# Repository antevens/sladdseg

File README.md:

# Sladdseg

Sladdseg is a wall plate that replaces a light switch on a circuit where every bulb is a smart bulb (here IKEA
Matter-over-Thread). The bulbs stay powered. An IKEA BILRESA scroll-wheel remote sits recessed in the plate and lifts
out; behind it a rocker switch cuts line and neutral to the circuit. The full edition adds mmWave presence,
temperature, humidity and push-to-talk voice at the switch location, powered from the box.

| North American single-gang (Decora) | European round flush box (DIN 49073) |
| --- | --- |
|  |  |

Two variants: **NA** for a 2 × 3 in single-gang box, **EU** for a Ø60 / 68 mm round flush box. Printed parts and
small PCBs, all generated from this repository.

## Design

- The remote is the control. The BILRESA sits in the plate, held by a magnet.
- The rocker is the fallback. Hidden behind the remote, it breaks line and neutral to the load and the plate's
  electronics; off and on brings the lights up without Home Assistant.
- Mains side: a certified rocker (Marquardt 1802.2504 or E-Switch RA412C1100), a certified 5 V supply and push-in
  terminal blocks, on a board designed to IEC 62368-1 spacing.

## Editions

| Edition | Remote | Mains board | Sensors | Face plate, NA | Face plate, EU |
| --- | --- | --- | --- | --- | --- |
| Switch | On its own cells | Rocker, terminal blocks | None | 69.85 × 114.3 mm (Decora) | 84.6 × 84.6 mm |
| Batt Free | Powered from the plate through spring pins, no cells | Rocker, terminal blocks, 5 V supply | None | 69.85 × 114.3 mm (Decora) | 84.6 × 84.6 mm |
| Full | Powered from the plate through spring pins, no cells | Rocker, terminal blocks, 5 V supply | Presence (mmWave, optional CO₂), temperature and humidity, push-to-talk microphone | 72.2 × 131.75 mm | 84.6 × 122.4 mm |

The barrier and the mains board are the same in every edition.

## What is on the plate

From the room inwards:

| Part | Material, place | Carries |
| --- | --- | --- |
| Face plate | PETG print, passive | Nothing: no electronics, no contacts, so it lifts off and goes back on blind. EU: snaps into a printed carrier that holds the sensor board |
| Sensor board | FR4, under the face plate, outside the box | The MSR-2 (ESP32-C3, LD2410B mmWave, optional CO₂) on its rear connector behind a thin radar skin; an SHT40 in a vented bay; a PDM microphone with its PDM-to-I²S converter. ESPHome over Wi-Fi; 5 V from the mains board |
| Barrier | PC-FR print, designed for a UL94 V-0 filament | The remote's pocket with the steel piece, the rocker's panel, and the wall between the mains volume and the low-voltage side |
| Pin board (Batt Free, Full) | FR4, in the box under the pocket floor | Two spring pins onto the back cover's pads |
| Mains board | FR4, in the box | The rocker, WAGO 2604 blocks for line, neutral and earth in and out, the 5 V supply on the switched side. The load runs in 0.5 mm copper bars on the front between the blocks and the rocker; every mains path sized for 15 A |

## Operation

Day to day the lights are controlled wirelessly: the remote, Home Assistant, the IKEA app or a voice assistant. The
rocker switch is for two cases:

- **Controller or network down:** turn the rocker switch off and on. The bulbs restart and come on at their power-on
  setting, which must be set to "On" in each bulb.
- **Safety:** off cuts line and neutral to the fixtures on this circuit and powers down the plate's electronics.

> **Warning: the rocker switch does not replace the breaker.** Turn the circuit's breaker off, and check with a
> tester that the wires are dead, before working on any wiring, the plate or the fixtures.

> **Warning: polarity matters.** Connect the supply's line to **L IN** and its neutral to **N IN**, as marked on the
> board, with the load wires on **L SW / N SW** (NA) or **L LOAD / N LOAD** (EU). Earth goes to **PE** on the NA board;
> on the EU plate it is joined in the box with a WAGO 221-412 lever connector. The PSU's fuse is
> in the line; with line and neutral swapped, the fuse sits in the neutral and line stays on the PSU when it blows.
> Confirm which supply wire is line with a tester before connecting.

The microphone (full edition) streams to Home Assistant's Assist pipeline only when listening is started from Home
Assistant. There is no wake word and no speaker.

## North American single-gang / Decora

Full edition:

| Remote in place | Remote out, rocker switch exposed |
| --- | --- |
|  |  |

| Half-section | Back, box side |
| --- | --- |
|  |  |

Exploded, front to back: remote, face plate, barrier, sensor board with the MSR-2, pin board with the spring pins on
two spacer posts, four nylon standoffs, mains board.

Switch edition:

| Remote in place | Remote out, rocker switch exposed |
| --- | --- |
|  |  |

Batt Free edition:

| Remote in place | Remote out, rocker switch exposed |
| --- | --- |
|  |  |

## European round flush box (DIN 49073)

The barrier closes the box and carries the remote; under it the mains board at the rocker's seat and the pin board;
on the wall the sensor board in a printed carrier, and the face plate snapped into the carrier.

Full edition:

| Remote in place | Remote out, rocker switch exposed |
| --- | --- |
|  |  |

| Half-section | Back, box side |
| --- | --- |
|  |  |

On the back: the mains board with its two WAGO push-in blocks (grey) and the PSU (black); the pin board sits between
it and the barrier.

Switch edition:

| Remote in place | Remote out, rocker switch exposed |
| --- | --- |
|  |  |

Batt Free edition:

| Remote in place | Remote out, rocker switch exposed |
| --- | --- |
|  |  |

## Battery-free back cover

For fixed installs: the printed cover replaces the remote's own and runs it from the plate with no cells; lifted
out, the remote is off. Two pads behind windows in the cover's back take 5 V from the spring pins, and a 3.3 V
regulator on the cover's flex feeds two spring fingers on the remote's battery contacts. Not a charging circuit; it
holds no energy.

| Cover with its flex | Exploded in the EU plate |
| --- | --- |
|  |  |

## Building from source

CAD in Python (build123d); boards in Python to KiCad 9 projects (ERC and DRC clean, schematic parity); slicer
projects; PCBWay packs; order lists with live DigiKey and Mouser stock. `make check`
includes a test that no air path leads from the mains volume through the printed barrier to the room.

```bash
make system-deps     # once, Ubuntu 24.04 (KiCad 9, headless slicer libs)
make setup           # once (venv + pinned ElegooSlicer)
make pcb             # boards: ERC / DRC, STEP, fab packs
make cad check       # CAD to build/, all checks (shared parts, NA, EU)
make na              # NA variant: CAD, checks, renders
make eu              # EU variant: CAD, checks, renders
make print           # ElegooSlicer projects in print/
make renders         # docs/renders/*.png
make order           # DigiKey / Mouser lists, PCBWay packs
```

| Document | Contents |
| --- | --- |
| [`AGENTS.md`](AGENTS.md) | Project overview, rules, status, backlog |
| [`docs/SAFETY.md`](docs/SAFETY.md) | Safety notes and limits |
| [`docs/DESIGN.md`](docs/DESIGN.md) | Requirements and decision log |
| [`docs/BOM.md`](docs/BOM.md) | Parts per plate |
| [`docs/ASSEMBLY.md`](docs/ASSEMBLY.md) | What holds each part, assembly order, detail views |
| [`docs/PRINTING.md`](docs/PRINTING.md) | Print jobs, settings, order of work |
| [`docs/MEASUREMENTS.md`](docs/MEASUREMENTS.md) | Measured values and the ones still estimated |
| [`pcb/README.md`](pcb/README.md) | All seven boards: what each carries, editions, status |
| [`pcb/na/README.md`](pcb/na/README.md), [`pcb/eu/README.md`](pcb/eu/README.md), [`pcb/shared/README.md`](pcb/shared/README.md) | Each variant's boards and the shared cover flex in detail: parts, nets, rules, board renders |
| [`pcb/order/README.md`](pcb/order/README.md) | DigiKey / Mouser order lists and PCBWay packs |

## Status

- **Ready to order:** the NA and EU mains boards and both pin boards have PCBWay packs, after
  the human review in [`pcb/na/fab/README.md`](pcb/na/fab/README.md) and [`pcb/eu/fab/README.md`](pcb/eu/fab/README.md).
- **Not ready to order:** the NA and EU sensor boards (CN2's position on the MSR-2 is a photo estimate) and the back cover
  flex (contact positions not yet measured on a remote).
- **To measure:** the `MEASURE` and `ESTIMATE` values in [`docs/MEASUREMENTS.md`](docs/MEASUREMENTS.md).
- **Not started:** the ESPHome configuration for the MSR-2 with the SHT40 and the microphone.

## Open items

Suitable for a contribution:

- a back cover with a battery and a charger;
- a UK variant (86 mm plate, shallow back box);
- a version for the BILRESA dual-button remote (IKEA E2489);
- a jumbo-plate option.

[`AGENTS.md`](AGENTS.md) has the conventions, the hard constraints and the checks that must stay green.

## Cost (2026-10-12)

Parts and PCBs per plate, USD.

| Package | 1 plate | 5 plates | 100 plates | 1,000 plates | 10,000 plates |
| --- | --- | --- | --- | --- | --- |
| NA full | 110.90 | 59.68 | 37.61 | 34.19 | 32.48 |
| NA full + MSR-2 | 148.89 | 97.67 | 75.60 | 72.18 | 70.47 |
| NA full + MSR-2 with CO2 | 168.89 | 117.67 | 95.60 | 92.18 | 90.47 |
| NA switch only | 20.68 | 15.96 | 10.00 | 9.06 | 8.60 |
| NA battery-free | 68.71 | 38.63 | 24.87 | 22.61 | 21.47 |
| EU full | 102.61 | 48.95 | 31.13 | 28.37 | 26.99 |
| EU full + MSR-2 | 140.60 | 86.94 | 69.12 | 66.36 | 64.98 |
| EU full + MSR-2 with CO2 | 160.60 | 106.94 | 89.12 | 86.36 | 84.98 |
| EU switch only | 15.59 | 9.18 | 6.64 | 6.04 | 5.74 |
| EU battery-free | 60.83 | 29.26 | 19.24 | 17.55 | 16.70 |

Sources and assumptions:

- **Parts at 1, 5 and 100 (sourced):** DigiKey US list prices for the order lists' parts (`pcb/order/`), cheapest
  packaging and price break for the total need, read 2026-10-12. Per plate:
  - 1 plate: NA full 50.97, NA battery-free 33.71, NA switch only 15.68; EU full 42.17, EU battery-free 25.83,
    EU switch only 10.59.
  - 5 plates: NA full 47.70, NA battery-free 31.63, NA switch only 14.96; EU full 36.86, EU battery-free 22.26,
    EU switch only 8.18.
  - 100 plates: NA full 34.20, NA battery-free 22.64, NA switch only 9.36; EU full 27.60, EU battery-free 16.92,
    EU switch only 6.00.
- **Parts at 1,000 and 10,000 (assumption):** 10 % and 15 % below the 100-plate price. DigiKey shows no prices
  above about 100 without a quote.
- **PCBs at 1 and 5 (sourced):** PCBWay's 5-piece minimum order, 2026-10-12; one plate pays for the whole order.
  - Mains board, pin board, EU mains board, EU pin board: 5.00 each order.
  - Sensor board 24.93, EU sensor board 25.44.
  - Cover flex: about 25 (estimate).
  - Per plate: 1 plate NA full 59.93, NA battery-free 35.00, EU full 60.44, EU battery-free 35.00, switch only
    5.00 (the mains board alone); 5 plates one fifth of that.
- **PCBs at 100 (sourced):** PCBWay quotes for 100 pieces, 2026-10-12.
  - Mains board 0.64, sensor board 1.17, pin board 0.36.
  - EU mains board 0.64, EU pin board 0.45, EU sensor board 1.21.
  - Cover flex 1.24.
  - Per plate: NA full 3.41, NA battery-free 2.23, EU full 3.53, EU battery-free 2.32, switch only 0.64.
- **PCBs at 1,000 and 10,000 (assumption):** the 100-piece price (no quote). This is cautious: board prices
  usually fall at volume.
- **MSR-2 (assumption):** Apollo's retail price at every quantity, 37.99 base and 57.99 with CO2. No volume price
  is published.

Known gaps:

- **Quote specs differ from the design:**
  - The mains boards were quoted with 1 oz copper; the NA board is 2 oz. The copper bars are not quoted.
  - The pin board was quoted at 1.6 mm, not 0.8.
- **Not included:**
  - PCB assembly (the sensor board, the EU sensor board and the cover flex need it);
  - the IKEA remote;
  - printed parts, screws and heatshrink;
  - shipping and duties.
- **Cheaper terminal blocks:** Same Sky TBL-0021-500-06GR (NA) and TBL-0020-500-02GR (EU), push-in without a lever,
  fit the WAGO 2604 footprint and cost about 5–6 (NA) and 3 (EU) less per plate at 100. Not in the design.

### Printed parts (own printer, 2026-10-13)

The barrier (one per variant, printed with the blank board for switch only, D-127) is printed in Elegoo PC-FR; the
face plate, the EU carrier and the back cover in Elegoo PETG. Grams and times come from the slicer projects
(`make print`). USD per plate.

| Package | Printed parts | Filament | Print time | Filament cost | Electricity | Printer wear | **Total** |
| --- | --- | --- | --- | --- | --- | --- | --- |
| NA full | Barrier and blank board 52.5 g PC-FR; face plate 23.8 g, back cover 8.1 g PETG | 84.4 g | 3.5 h | 1.56 | 0.08 | 0.31 | **1.94** |
| NA switch only | Barrier and blank board 52.5 g PC-FR; face plate 16.7 g PETG | 69.2 g | 2.8 h | 1.39 | 0.06 | 0.25 | **1.70** |
| NA battery-free | Barrier and blank board 52.5 g PC-FR; face plate 16.7 g, back cover 8.1 g PETG | 77.3 g | 3.2 h | 1.48 | 0.07 | 0.28 | **1.84** |
| EU full | Barrier and blank board 13.3 g PC-FR; face plate 43.3 g, carrier 18.5 g, back cover 8.1 g PETG | 83.3 g | 3.0 h | 1.08 | 0.07 | 0.27 | **1.41** |
| EU switch only | Barrier and blank board 13.3 g PC-FR; face plate 30.2 g, carrier 8.6 g PETG | 52.1 g | 1.9 h | 0.73 | 0.04 | 0.17 | **0.94** |
| EU battery-free | Barrier and blank board 13.3 g PC-FR; face plate 30.2 g, carrier 8.6 g, back cover 8.1 g PETG | 60.2 g | 2.3 h | 0.82 | 0.05 | 0.20 | **1.08** |

Sources and assumptions:

- **Filament (sourced):** Elegoo US store, 10 kg packs, read 2026-10-12.
  - PC-FR: 229.99, 23.00 / kg (1 kg spool 34.99).
  - PETG Pro: 109.99, 11.00 / kg (1 kg spool 13.99).
- **PETG weights (assumption):** the face plates and carriers are sliced in PLA only. Their weight is scaled by
  the density ratio (PETG 1.27 / PLA 1.24) at the same print time.
- **Electricity (assumption):** 150 W average at 0.15 / kWh.
- **Printer wear (assumption):** about 440 for the CC2 Combo (Elegoo's bundles list at 435–499) over 5,000 print
  hours.
- **Not included:** labour, failed prints, bed adhesive.
- **Print services:** not quoted.

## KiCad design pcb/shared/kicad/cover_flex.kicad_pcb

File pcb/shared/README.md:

# Shared board (v0.7)

The replacement back cover's flex (D-35, D-50), the same board in both variants, and the generator for every
low-voltage board: `tools/gen_lv.py na|eu|shared` writes the NA sensor and pin boards into `../na/kicad/`, the EU
sensor board into `../eu/kicad/` and the cover flex into `kicad/`, each folder with the low-voltage library (`lv.pretty`,
`lv.kicad_sym`). Parts both variants share (the CN2 mate, the microphone and its parts, footprints, the flex) are in
`tools/lv_parts.py`; each variant's boards in `../na/tools/lv_parts_na.py` and `../eu/tools/lv_parts_eu.py`. Geometry
comes from `cad/build123d/params.py` (the CAD model is in `cad/build123d/backcover.py`).

Nothing here touches mains.

## Back cover flex (`kicad/cover_flex.*`)

Single copper layer, polyimide, for the replacement back cover that powers a BILRESA E2490
without cells (`cad/build123d/backcover.py`, DESIGN D-35). Drawn flat, seen from the copper side.

- J1, J2: gold pads (+5V, GND) on the pad section, which lies copper down on a ledge in the
  cover, behind Ø2.1 windows in its back: the plate's spring pins press on them (NA, D-50). Ø3.0 copper
  under a Ø2.6 coverlay opening: the coverlay holds the pad's edge (D-116).
- A 2.6 mm run (in a notch along the GND contact post's inner face, D-79) to the terminal end; one 90°
  bend, inside r 0.6 mm (6 × the 0.10 mm flex), copper outside, with a relief slit either side of the
  run so the rest of the end section reaches down to the ledge (D-116). The tracks cross the bend zone
  straight; the +3V3 lane turns 0.85 mm past it.
- J1 takes +5 V from the plate (D-41, D-50); D1 TI TPD1E10B06DYAR (ESD) on +5V; U1 TI TLV75533PDBVR (3.3 V,
  SOT-23-5) with C3 / C4 1 µF 0603 X5R (0.85 µF or more at their working voltages) on the regulator section,
  copper down in a recess in the cover (0.4 mm wall left), feeds VBAT (D-116).
- A 0.8 mm FR4 stiffener (back side) on the pad and regulator sections, flush with their long
  edges: five snap hooks in the cover hold it down against the pins' push (D-45, D-79); 0.15 mm under
  the hooks for the stiffener's tolerance and adhesive (D-116). No holes.
- Coverlay openings 0.1 mm beyond the pads, one opening over each pin row of U1 / D1; teardrops where the
  tracks leave the pads (D-116).
- J3, J4: Harwin S7081-42R spring fingers (VBAT, GND) on the end section, on the cell axes, long
  axis vertical with the bend end up (the battery contacts ride down the arm's ramp as the cover
  goes on), on a 0.4 mm FR4 stiffener (back side), notched round the run 0.76 mm past the bend zone; it slides
  down slots along the contact blocks (D-55). The end section stands 2.0 mm (the fingers'
  working height) in from the cell end plane: J3 presses the remote's fixed VBAT plate, J4 its GND
  leaf spring (finger and leaf share the travel). Between them only a band passes under the
  remote's PCB strip.

Not ready to fabricate: the positions come from the FCC internal photos (REF) or are MEASURE;
`tools/build.sh` writes no `fab/cover_flex/` while `COVER_CONFIRMED` is false.

## Microphone firmware (D-29, D-83)

ESPHome on the MSR-2, push-to-talk: Home Assistant starts listening (for example from a BILRESA
button automation calling the action) and the voice pipeline ends it on silence. Untested
starting point:

```yaml
i2s_audio:
  - id: i2s_mic_bus
    i2s_lrclk_pin: GPIO6
    i2s_bclk_pin: GPIO4

microphone:
  - platform: i2s_audio
    id: plate_mic
    i2s_audio_id: i2s_mic_bus
    adc_type: external
    i2s_din_pin: GPIO7
    channel: left              # SELECT low: check which slot carries the mic on an MSR-2
    bits_per_sample: 32bit     # ADAU7002: 20-bit data in 32-bit slots, BCLK = 64 x fs
    sample_rate: 16000         # PDM clock 64 x fs = 1.024 MHz: the mic's performance mode starts at 1.0 MHz

voice_assistant:
  microphone: plate_mic

api:
  actions:
    - action: start_listening
      then:
        - voice_assistant.start:
    - action: stop_listening
      then:
        - voice_assistant.stop:
```

Open: whether the pipeline accepts 48 kHz from this microphone on the C3 or needs 32 kHz, and
the C3's RAM / CPU headroom next to the radar, Wi-Fi and BLE.

## Regenerate

```bash
make pcb        # every board; or pcb/shared/tools/build.sh for the cover flex alone
```

`tools/build.sh` writes the 3D models and the cover flex (`tools/gen_lv.py shared`), runs ERC and DRC (all severities,
schematic parity; reports in `build/`) and writes `fab/cover_flex/` once its positions are measured
(`COVER_CONFIRMED`).

## Open

- CN2 mate (Molex 55909-2474, D-82, D-89): contact map and pin 1 (from the GPIO add-on's plug or Apollo). Then set
  `CN2_CONFIRMED`, regenerate, check the fan-out. The pads' mask webs are 0.18 mm (PCBWay: 0.19 green): one opening
  per row.
- The FFC passes through the mains volume to the barrier's slit (SAFETY item 4).
- MK1 and U2 pin 1 against parts (footprints from the datasheets' top views).
- Microphone firmware test on an MSR-2 (sample rate, I²S slot, load).

## Renders

The cover flex with components, without them, and its copper layer.

| Back cover flex, copper side | Back cover flex, stiffener side |
| --- | --- |
|  |  |
|  |  |

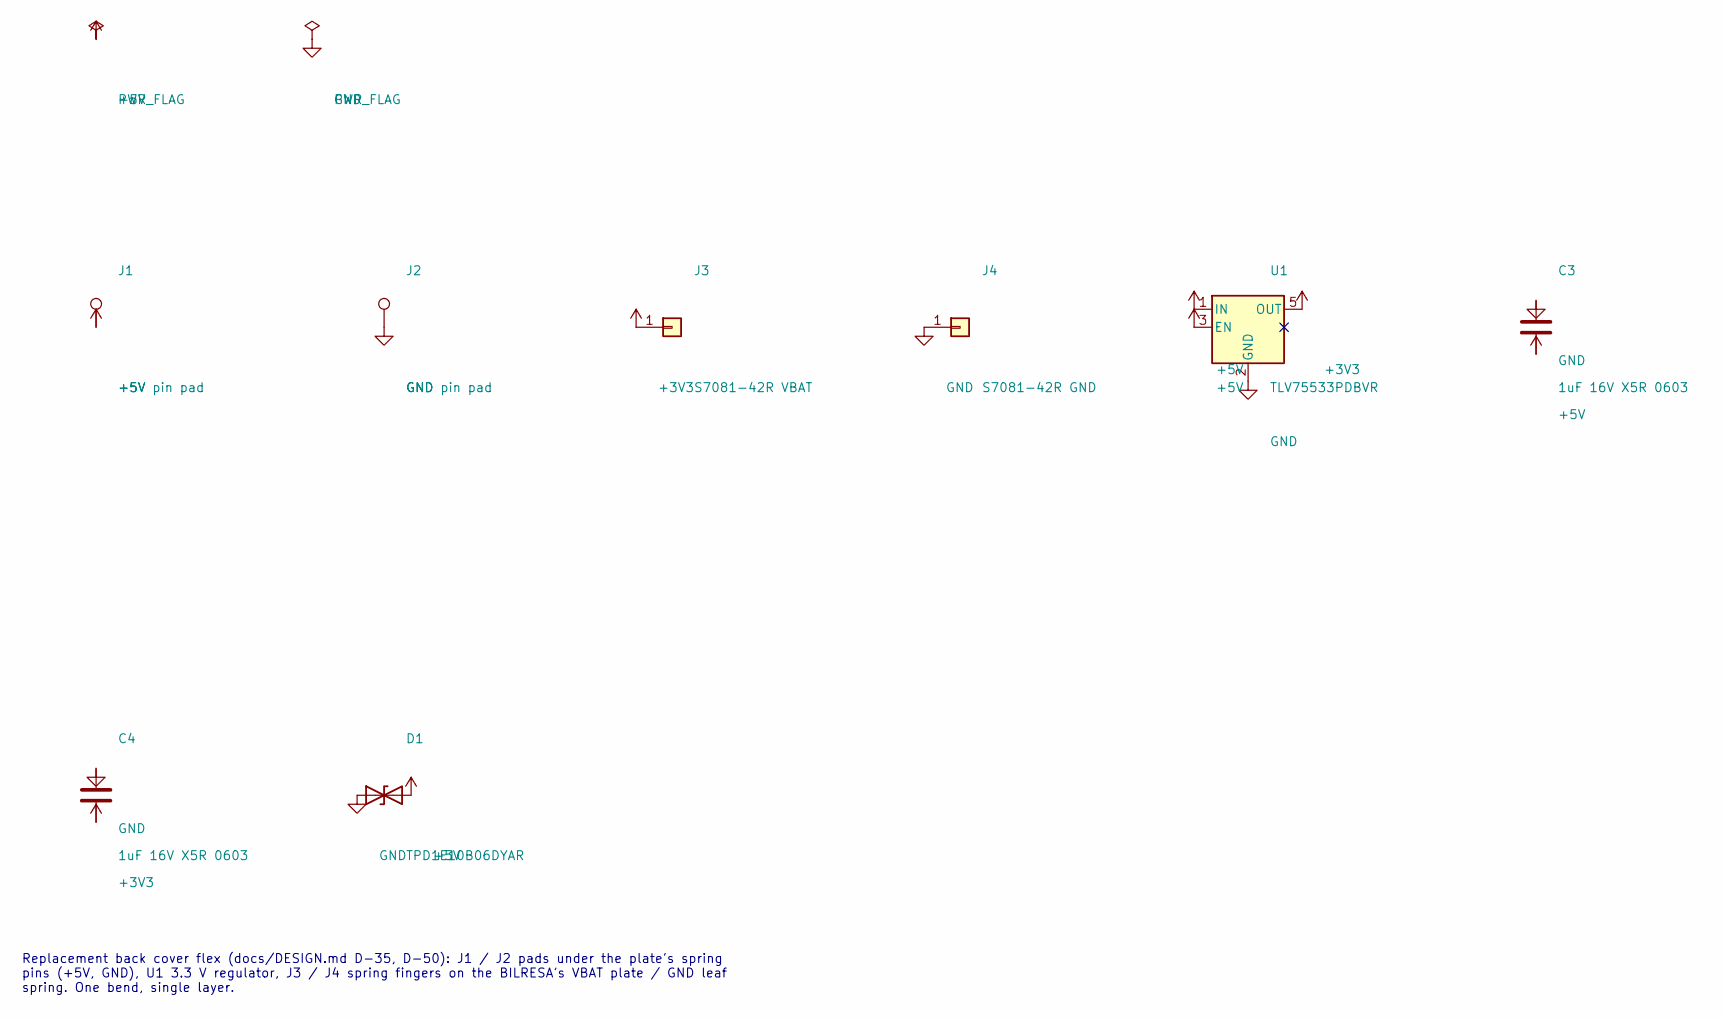
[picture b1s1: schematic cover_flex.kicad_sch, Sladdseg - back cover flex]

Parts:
C3, C4: 1uF 16V X5R 0603; C_0603_1608Metric; MPN CL10A105KO8NNNC
D1: TPD1E10B06DYAR; D_SOD-523_TI_DYA0002A; MPN TPD1E10B06DYAR
J1: +5V pin pad; Contact_Pad_D2.6mm
J2: GND pin pad; Contact_Pad_D2.6mm
J3: S7081-42R VBAT; Harwin_S7081-42R; MPN S7081-42R
J4: S7081-42R GND; Harwin_S7081-42R; MPN S7081-42R
U1: TLV75533PDBVR; SOT-23-5; MPN TLV75533PDBVR

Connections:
+3V3: C4.2, J3.1, U1.5 (OUT)
+5V: C3.2, D1.2 (A2), J1.1, U1.1 (IN), U1.3 (EN)
GND: C3.1, C4.1, D1.1 (A1), J2.1, J4.1, U1.2 (GND)

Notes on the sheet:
Replacement back cover flex (docs/DESIGN.md D-35, D-50): J1 / J2 pads under the plate's spring pins (+5V, GND), U1 3.3 V regulator, J3 / J4 spring fingers on the BILRESA's VBAT plate / GND leaf spring. One bend, single layer.

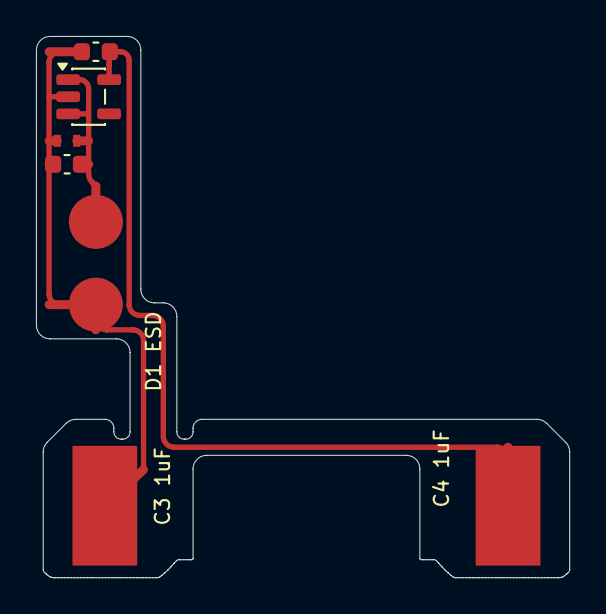
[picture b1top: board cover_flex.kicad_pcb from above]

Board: 2 copper layers, 29.6 x 30.1 mm, 8 parts (0 on the bottom side), 3 nets.

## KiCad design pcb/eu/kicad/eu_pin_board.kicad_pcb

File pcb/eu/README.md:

# EU boards (v0.7)

The European plate's boards (round flush box, DIN 49073, Ø60 inside): the mains board and the pin board, both
hanging from bosses under the barrier, from `tools/gen_eu.py` with their parts in `tools/parts_eu.py` (D-30, D-36); the
sensor board in the carrier from `../shared/tools/gen_lv.py eu`, its parts in `tools/lv_parts_eu.py` (D-56, D-70).
Geometry from `cad/build123d/params.py` and `cad/build123d/eu/params_eu.py`. The back cover's flex, the same for both
variants, is in `../shared/README.md`.

Spacing values are design targets for human review. Nothing here is a compliance claim.

## Mains board (`kicad/eu_mains_board_busbar.*`, fab pack in `fab/eu_mains_board_busbar/`)

Round, at the rocker's PCB seat (16.2 mm below its panel face). The rocker breaks line and neutral
of the lights; the PSU is fed from the switched side, so the rocker also turns the sensor off. The lights' current
runs in four copper bars on the front (D-153); the earlier board with the load in pours on high-CTI FR4 is dropped
(D-155).

| Ref | Part | Side | Nets |
| --- | --- | --- | --- |
| S1 | Marquardt 1802.2504 rocker, DPST, PCB pins, ENEC 12(4) A 250 V~, UL/CSA 15 A; second source E-Switch RA412C1100 (4.8 mm tabs, ENEC 10(4) A, D-88): plated slots 5.2 × 1.2 on 10.2 × 7.05, their pads up to the WAGO bodies (0.05 mm), 3.85 mm from the WAGO pins (D-153) | front (through the barrier's panel) | 1 L_IN, 1a L_SW, 2 N_IN, 2a N_SW |
| J1 | WAGO 2604-3102, push-in, 2-pole, 4 mm², entry 90° to the board, 400 V III/2; turned 180° from J2 | back | L_SW (pole 1), L_IN (pole 2, upper) |
| J2 | WAGO 2604-3102 (as J1) | back | N_IN (house neutral), N_SW (to the lights) |
| F1 | Schurter UMT 250, T1A 250 VAC | front | L_SW to L_F |
| RV1 | TDK CU4032K275G2, 275 VAC | front | L_F to N_SW |
| PS1 | Zettler ZPI03S0500WC, 5 V 600 mA (UL/EN 62368-1, EN 61558-2-16; I/P-O/P 3600 VAC; reinforced / OVC not stated: review, D-100) | back | inputs L_F / N_SW above the slot, outputs +5V / GND below it |
| J3 | Samtec TSM-102-02-L-SV, SMT pin header 1x2, 2.54 mm, 8.13 mm post (no pin tails under the PSU) | front, 5 V island | +5V, GND |
| MH1-MH3 | M2 holes on the barrier's long bosses | - | - |

- The lights' current runs in four straight 0.5 mm copper bars soldered on the front, one along each WAGO pole's pin
  row to the rocker (`BB_BARS`: in bars above their row, switched below it, round ends past the outer pin, clear of
  the 6 mm barrier bosses); no load pours. Built by `gen_eu.py busbar`; `tools/bars_eu.py` (CAD Python) draws the
  bars round the pads (`build/eu_mains_board_pads.json`), checks them and writes `kicad/eu_mains_board_busbar_bars.json`
  (their lands: copper with no solder mask) and the DXF for the laser cutter. WAGO pin rows and body from WAGO's 3D
  model (8.2 mm apart, levers towards the board centre, where the blocks' pins stay 1.0 mm clear of the rocker body
  on the front); blocks at x ±16.6, y 7.5. Short links from the bars to F1 and to the RV1 / PSU feed (1.0 mm track).
  Standard FR4, 1 oz (no PE on the board), HASL lead-free.
- A routed relief slot under the PSU, between its input and output rows, cuts off the 5 V island
  (PSU outputs, J3). Mains copper keeps ≥ 8 mm (clearance and creepage) from it.
- Keep-out areas round the mounting holes: mains copper ≥ 1.0 mm from them.
- No PE on the board: the lights' protective earth is joined in the box in a WAGO 221-412 lever connector, in the
  order lists (D-94; a third PE conductor takes a 221-413).
- Installer labels on the back: L IN / L LOAD, N IN / N LOAD at the WAGO blocks, MAINS 230 VAC.

## Pin board (`kicad/eu_pin_board.*`, fab pack in `fab/eu_pin_board/`)

D-shaped, just under the barrier, cut below the switch cup; a hole lets the mains board's lower long
boss through. No mains on it.

| Ref | Part | Side | Nets |
| --- | --- | --- | --- |
| J1 | Samtec SSW-102-01-G-S pin socket 1x2, 2.54 mm (8.5 mm), on the mains board's J3 | back | +5V, GND |
| C1 | 22 µF 10 V X5R 1206 | front | +5V to GND |
| P1, P2 | Harwin P70-2200045 SMT spring pins with pegs, 2 A | front | GND (P1, upper), +5V (P2): through the barrier onto the sensor board's pads (D-56, D-59, D-70) |
| P3, P4 | Harwin P70-2200045 SMT spring pins with pegs, 2 A | front | +5V (P3, upper), GND (P4): through the barrier onto the battery-free back cover's pads (D-54, D-79) |
| MH1, MH2 | M2 holes on the barrier's bosses | - | - |

The header posts reach 3.07 mm into the socket (boards 16.1 mm apart, D-59; check with the parts).
Nothing is soldered or wired between the boards or across the barrier (DESIGN R9, R10).

## Sensor board (`kicad/eu_sensor_board.*`)

FR4 1.6 mm, two layers, round the remote pocket in the barrier's printed carrier (its rim round the board). TP1 / TP2:
Ø2.4 gold pads on the underside under the pin board's sensor spring pins (GND, +5V). As on the sensor board: J2 mates
the MSR-2's CN2 (Hirose DF40C-24DP-0.4V(51), Apollo's contact map, D-154) and H5–H7 (Würth WA-SMSI 9774015243R, 1.5 mm) carry its board under the face plate's
posts; MK1 and U2 with C3, C4 and R1 as on the sensor board (`route_mic`, D-83), the mic at x 32.0 so its parts and
lanes sit between it and the MSR-2's bay frame. I²S from CN2's signal row (the lower one) down, right, down and into U2,
+3V3 down to a via and on the back to the parts' +3V3; SDA and SCL out past the header's ends to vias; SDA, SCL and
+3V3 (from the parts' +3V3) on the back
down the outer left edge (outside the snap windows and the screws) to U1 (SHT40) and C2 at the bottom; +5V from the
pin pad on the back up the outer right edge and across to a via above CN2's +5V contact; GND pours on both layers; 0.45 / 0.2 mm vias round CN2. Windows at
the four corners pass the face plate's snap fingers; notches in the top edge clear the MSR-2's back switches. H1–H4:
holes for the M2 screws into the carrier. Fit-test prototype: CN2's position on the MSR-2 is a photo estimate.

## Rules

`kicad/eu_mains_board_busbar.kicad_dru`: L–N ≥ 3.2 mm, any two different mains nets ≥ 3.2 mm (line / switched
line / fused line, neutral / switched neutral; `BB_GAP`: IEC 60664-1 creepage at the 320 V row, pollution degree 2,
material group III, standard FR4, D-153), mains to the 5 V side ≥ 8.0 mm (clearance and creepage), mains copper
≥ 1.0 mm from the board edge and the holes; pins of one rated part keep the part's own spacing. Design targets for
human review, not a compliance claim.

The net classes come from the project file; `tools/gen_eu.py` rewrites it after every save
(pcbnew's SaveBoard resets it). The single EU PSU board before D-36 was checked without them, so
its isolation was never verified by DRC.

## Regenerate

```bash
make pcb        # every board; or pcb/eu/tools/build.sh for the EU boards alone
```

`tools/build.sh` writes the 3D models, the mains board and the pin board (`gen_eu.py`) and the sensor board
(`../shared/tools/gen_lv.py eu`), runs ERC and DRC on all three, and writes the PCBWay packs for the mains board and
the pin board in `fab/` (`fab/README.md`: order settings and the review checklist). Order only after the review and a
dry fit of the stack in a real box. The sensor board's PCBWay files are a fit-test prototype (D-154).

## Renders

Each board with components, without them, and its copper layers (back seen from behind).

| Mains board, front | Mains board, back |
| --- | --- |
|  |  |
|  |  |
|  |  |

Dropped board (D-155), its files still in the tree until backlog item 4 removes them: `kicad/eu_mains_board.*`,
`fab/eu_mains_board/`, `build/eu_mains_board.step` and the renders `docs/renders/eu_mains_board_front.png`,
`docs/renders/eu_mains_board_back.png`, `docs/renders/eu_mains_board_bare_front.png`,
`docs/renders/eu_mains_board_bare_back.png`, `docs/renders/eu_mains_board_copper_front.png`,
`docs/renders/eu_mains_board_copper_back.png`, `docs/renders/eu_mains_board_bare_iso.png`.

| pin board, front | pin board, back |
| --- | --- |
|  |  |
|  |  |
|  |  |

| Sensor board, front | Sensor board, back |
| --- | --- |
|  |  |
|  |  |
|  |  |

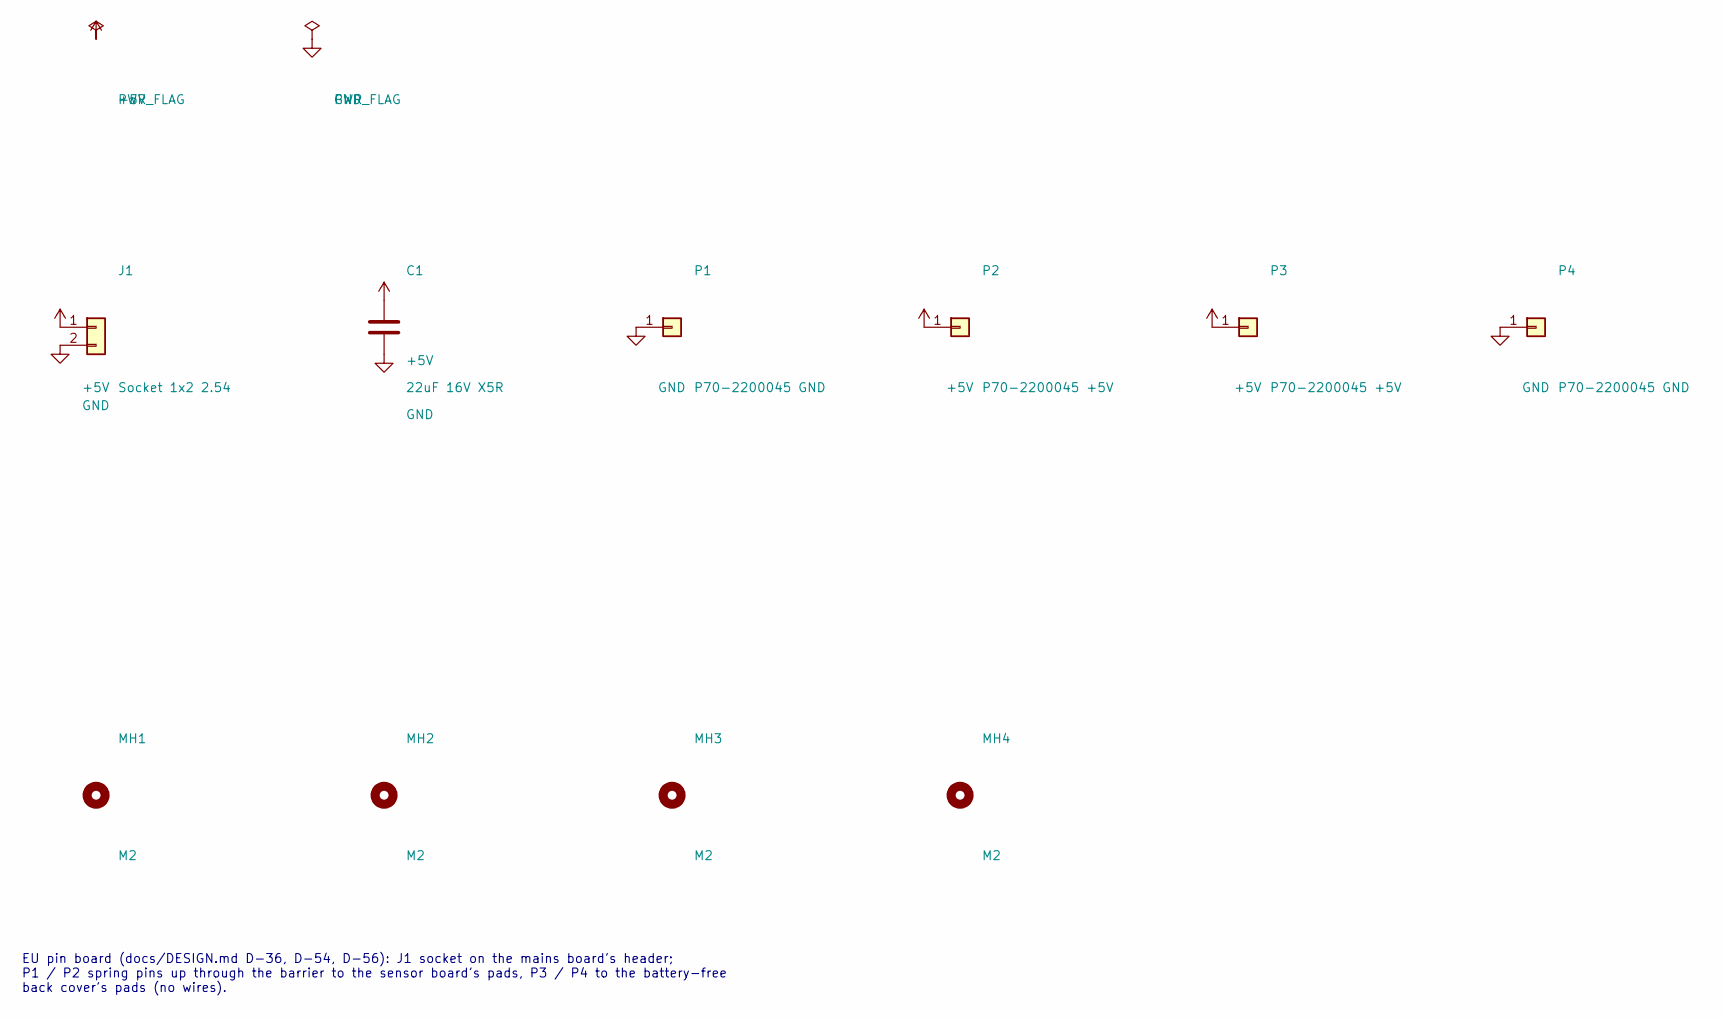
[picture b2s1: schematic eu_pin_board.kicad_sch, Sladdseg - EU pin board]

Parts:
C1: 22uF 16V X5R; C_1206_3216Metric; MPN C1206C226M4PACTU
J1: Socket 1x2 2.54; PinSocket_1x02_P2.54mm_Vertical; MPN SSW-102-01-G-S
MH1, MH2, MH3, MH4: M2; MountingHole_2.2mm_M2
P1, P4: P70-2200045 GND; Harwin_P70-2200045; MPN P70-2200045
P2, P3: P70-2200045 +5V; Harwin_P70-2200045; MPN P70-2200045

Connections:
+5V: C1.1, J1.1, P2.1, P3.1
GND: C1.2, J1.2, P1.1, P4.1

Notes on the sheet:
EU pin board (docs/DESIGN.md D-36, D-54, D-56): J1 socket on the mains board's header; P1 / P2 spring pins up through the barrier to the sensor board's pads, P3 / P4 to the battery-free back cover's pads (no wires).

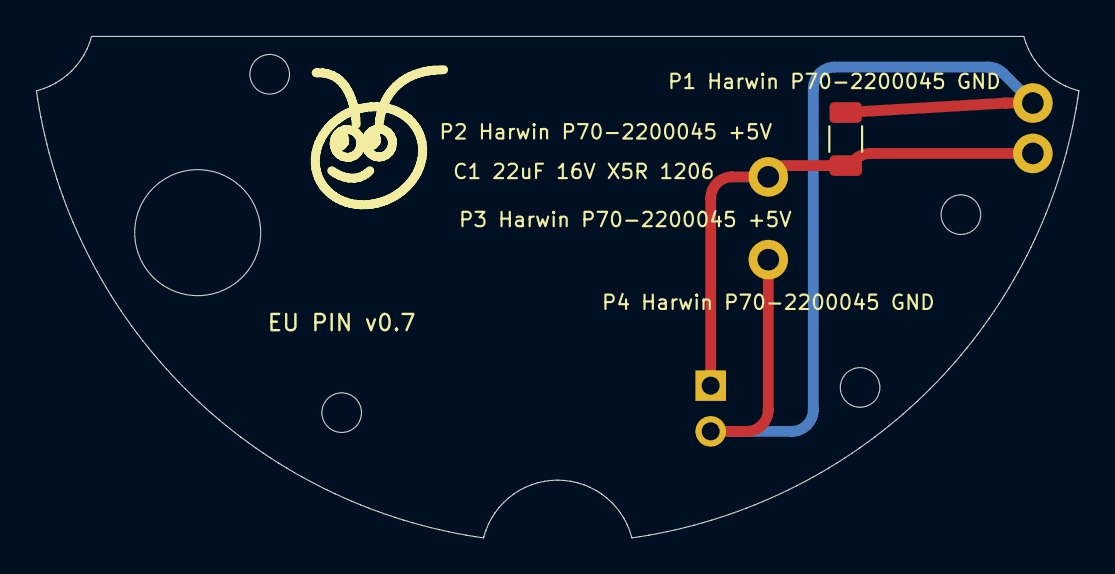
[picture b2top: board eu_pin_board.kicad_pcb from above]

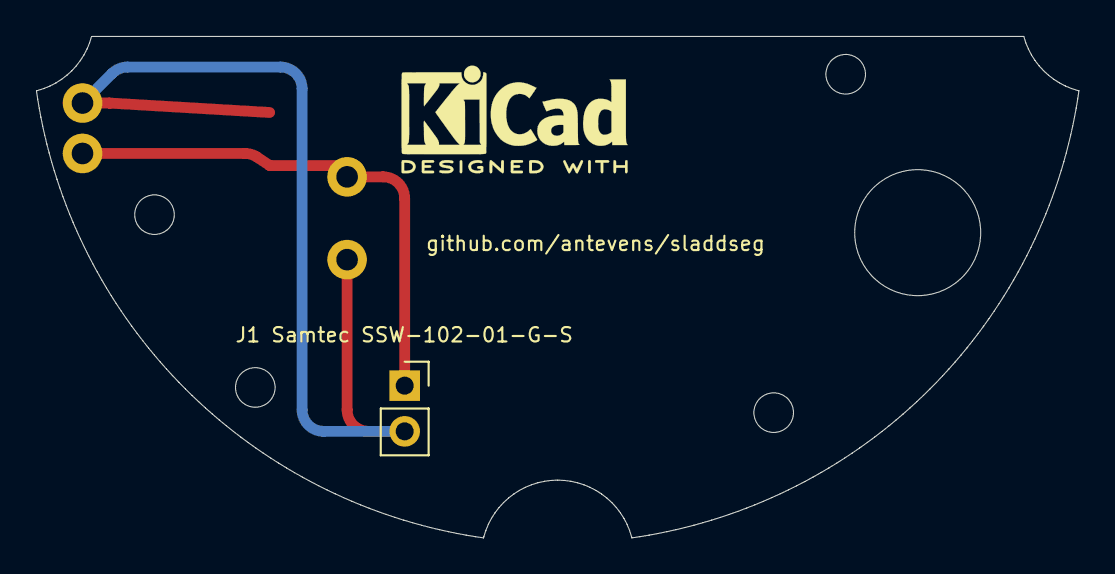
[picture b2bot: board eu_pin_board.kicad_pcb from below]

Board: 2 copper layers, 57.9 x 27.9 mm, 12 parts (2 on the bottom side), 2 nets.

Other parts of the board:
LOGO1: Ant_Logo_8mm_SilkScreen
LOGO2: KiCad-Logo2_5mm_SilkScreen

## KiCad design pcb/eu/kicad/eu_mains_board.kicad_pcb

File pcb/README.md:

# Boards (v0.7)

Seven boards, generated from Python into KiCad 9 projects (ERC and DRC at all severities, schematic parity), in one
folder per variant and one for the board both variants share. Spacing values are design targets for human review.
Nothing here is a compliance claim, and nothing has been checked by a third party.

| Folder | Boards | Details |
| --- | --- | --- |
| `na/` | NA mains board, sensor board, pin board | [`na/README.md`](na/README.md) |
| `eu/` | EU mains board, pin board, sensor board | [`eu/README.md`](eu/README.md) |
| `shared/` | back cover flex; the low-voltage board generator for both variants | [`shared/README.md`](shared/README.md) |
| `tools/` | helpers every generator uses (`kigen.py`, `fplib.py`, `common_parts.py`, `gen_3d.py`), renders, order lists | - |
| `order/` | DigiKey / Mouser order lists and PCBWay packs | [`order/README.md`](order/README.md) |

| Board | Editions | Size, material | Carries | Status |
| --- | --- | --- | --- | --- |
| NA mains board (bus bars, D-153) | all | 47 × 72 mm, standard FR4 1.6 mm, 2 oz, HASL, 2 layers | rocker switch S1, WAGO 2604-1106 (L / N / PE in and out), F1, RV1, Mean Well IRM-03-5, J2 (5 V FFC), spacer posts P1 / P2; four 0.5 mm copper bars on the front (J1 – S1), PE ring both sides, closed slot under PS1; switch only: S1 and J1 alone | PCBWay pack and bar DXF in `na/fab/na_mains_board_busbar/` |
| NA sensor board | full | 66.3 × 125.9 mm, FR4 1.6 mm, 2 layers | J1 (5 V FFC), J2 (MSR-2's CN2), SHT40, microphone + ADAU7002 | fit-test prototype: CN2's position on the MSR-2 estimated |
| NA pin board | battery-free, full | 14 × 12 mm, FR4 0.8 mm, 2 layers | two Harwin P70 spring pins onto the back cover, on the mains board's spacer posts | PCBWay pack in `na/fab/na_pin_board/` |
| EU mains board (bus bars, D-153) | all | Ø58 mm, standard FR4 1.6 mm, 1 oz, HASL, 2 layers | rocker switch S1, two WAGO 2604-3102, F1, RV1, Zettler ZPI03S0500WC, J3 (5 V header); four straight 0.5 mm copper bars on the front (J1 / J2 – S1); switch only: S1, J1, J2 alone | PCBWay pack and bar DXF in `eu/fab/eu_mains_board_busbar/` |
| EU pin board | battery-free, full | 58 × 27.9 mm D-shape, FR4 1.6 mm, 2 layers | socket on the mains board's J3, C1, four Harwin P70 spring pins (sensor board, back cover) | PCBWay pack in `eu/fab/eu_pin_board/` |
| EU sensor board | full | 76 × 113.8 mm, FR4 1.6 mm, 2 layers | pads for the pin board's spring pins, J2 (MSR-2's CN2), SHT40, microphone + ADAU7002 | fit-test prototype: CN2's position on the MSR-2 estimated |
| Back cover flex | battery-free, full (both variants) | 31.2 × 30.1 mm flat, polyimide 0.10 mm, 1 copper layer, FR4 stiffeners | pads for the spring pins, ESD diode, 3.3 V regulator, two spring fingers onto the remote's cell contacts | no fab files: contact positions not measured on a remote |

| NA mains board | NA sensor board | NA pin board |
| --- | --- | --- |
|  |  |  |

| EU mains board | EU pin board | EU sensor board |
| --- | --- | --- |
|  |  |  |

| Back cover flex |
| --- |
|  |

## Silkscreen labels and 3D models (all boards)

Every part carries a silkscreen label with its reference and maker / model (value and size for
generic passives; net names on bare contact pads), on the side it is mounted, placed by
`tools/kigen.py` (`place_labels`): next to the part, clear of pads, other silkscreen, other parts'
courtyards and the board outline (slots included). On a single-layer flex with no room on the
copper side the label goes on the bare back. ERC / DRC (all severities) check the result.

3D models come from `tools/gen_3d.py` into each project's `kicad/3d/`: a vendor STEP from
`scratch/3d/` when present (moved into footprint coordinates by its entry), otherwise an envelope
from the datasheet dimensions. Vendor files stay in the git-ignored `scratch/` (their terms).

| Model | Source now | Vendor model |
| --- | --- | --- |
| Traco TMPS 03 | vendor (tracopower.com, 3D drawings; pins checked against the pads) | in use |
| Mean Well IRM-03, Hirose FH12-6S, Samtec TSM (EU J3), 0402 / 1206 passives | KiCad library | in use |
| Schurter UMT 250 | envelope | <https://www.schurter.com/en/datasheet/UMT%20250> |
| TDK SIOV CU4032K275G2 (B72660M0271K093) | envelope | <https://product.tdk.com/en/search/sensor/protect/varistor/info?part_no=B72660M0271K093> |
| WAGO 2604-3102 | vendor (wago.com, CADENAS; pins checked against the pads) | in use |
| WAGO 2604-1106 | vendor (wago.com, CADENAS; pins checked against the pads) | in use |
| Marquardt 1802.2504 | vendor 1802.1108 housing (Marquardt LIB_1802.1108; same 1802 flange, rocker, body) on the 1802.2504 underside from its drawing (body to 11.7, pin stems to the 16.2 seat, 0.8 pins; pins checked against the pads) | 1802.2504 itself: on request from Marquardt |
| Harwin P70-2200045 | envelope | <https://www.harwin.com/products/P70-2200045/> |
| Harwin S7081-42R | envelope (shape from the drawing) | <https://www.harwin.com/products/S7081-42R/> |
| Knowles SPK0641HT4H-1 | envelope (top port marked) | <https://www.knowles.com/docs/default-source/model-downloads/spk0641ht4h-1-rev-a.pdf> |
| Analog Devices ADAU7002 (WLCSP-8) | envelope | <https://www.analog.com/en/products/adau7002.html> |
| Sensirion SHT40 (DFN-4) | envelope | <https://sensirion.com/products/catalog/SHT40> |

To use a vendor model: put its STEP in `scratch/3d/`, add the file name and its transform to the
entry in `tools/gen_3d.py`, run `make pcb`, and check the pins against the pads (export the board
to STEP).

## Regenerate

Needs KiCad 9 (`kicad-cli` and the `pcbnew` Python module) and the repository's `.venv` with build123d.

```bash
make pcb        # na/tools/build.sh, eu/tools/build.sh, shared/tools/build.sh
```

Each `build.sh` writes the 3D models (`tools/gen_3d.py`), the libraries, projects and rules, schematics and boards of
its folder, runs ERC and DRC (reports in `build/`) and writes the fab packs that are not blocked. Footprints and symbols
shared by every board come from `tools/fplib.py`; each project folder's lib tables list its own library and the
low-voltage library (`lv`).

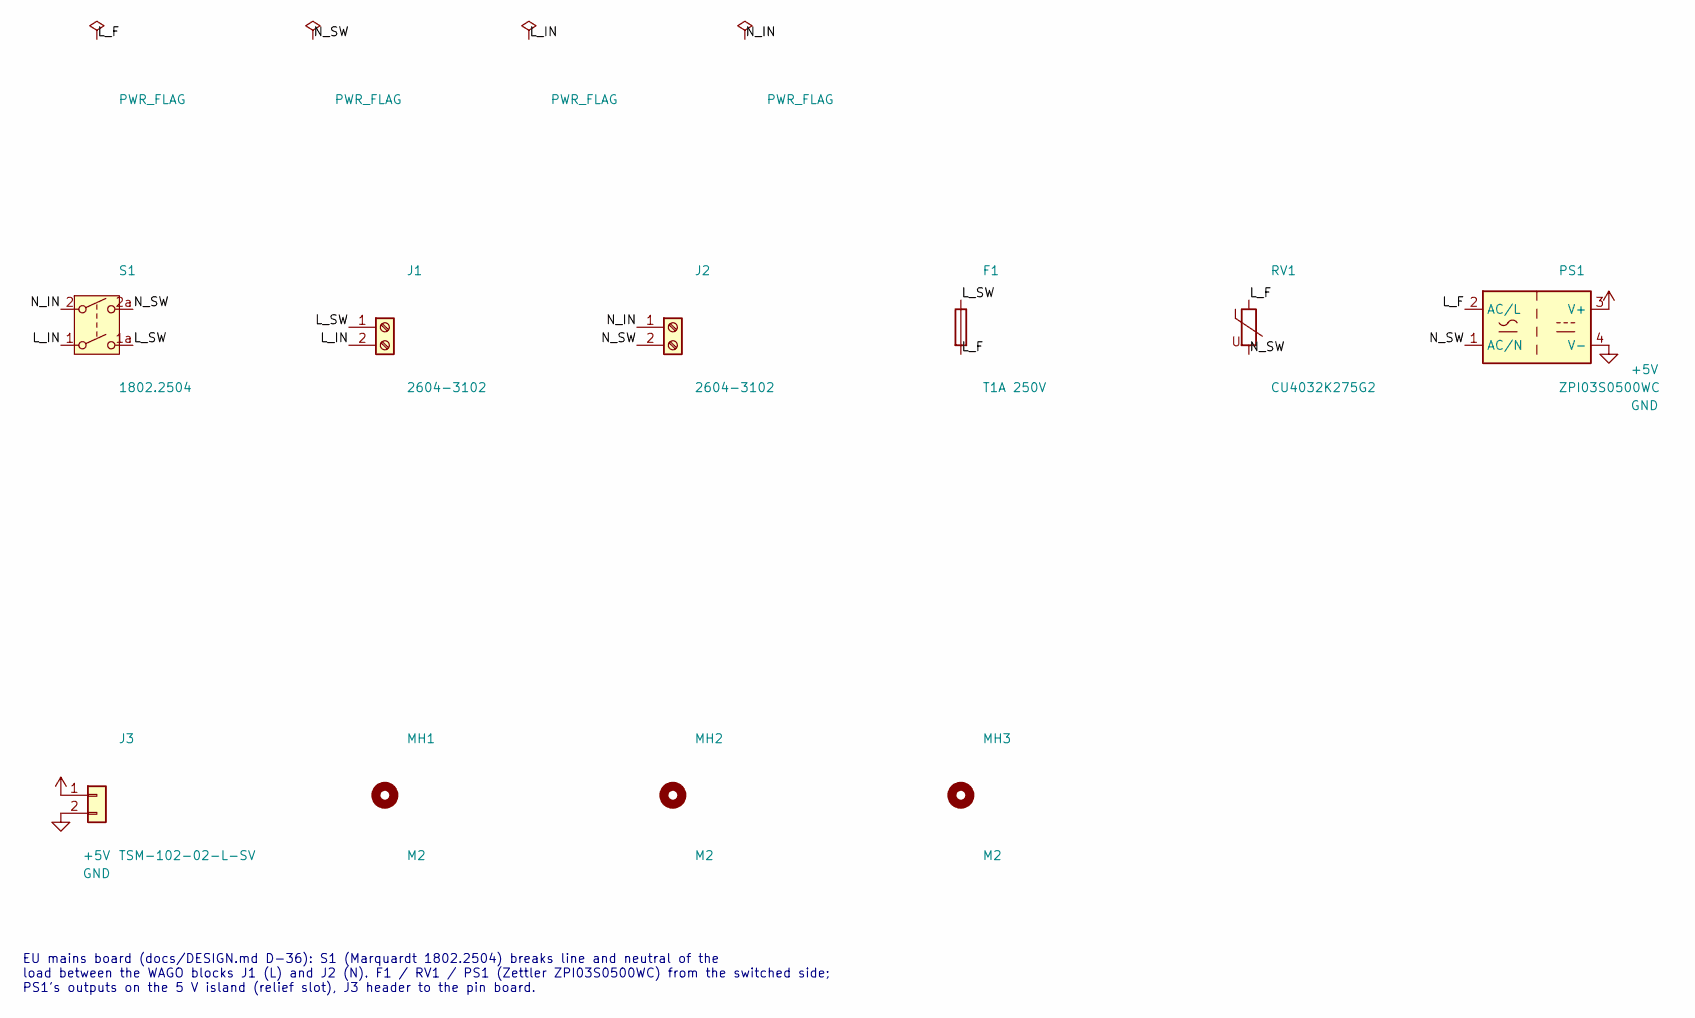
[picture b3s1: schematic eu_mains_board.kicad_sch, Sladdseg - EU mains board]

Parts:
F1: T1A 250V; Fuse_Schurter_UMT250; MPN 3403.0166.11
J1, J2: 2604-3102; WAGO_2604-3102_1x02_P5.00mm_Vertical; MPN 2604-3102
J3: TSM-102-02-L-SV; PinHeader_1x02_P2.54mm_Vertical_SMD_Pin1Left; MPN TSM-102-02-L-SV
MH1, MH2, MH3: M2; MountingHole_2.2mm_M2
PS1: ZPI03S0500WC; Converter_ACDC_Zettler_ZPI03_THT; MPN ZPI03S0500WC
RV1: CU4032K275G2; Varistor_TDK_CU4032; MPN B72660M0271K093
S1: 1802.2504; Rocker_DPST_Marquardt_1802.2504_E-Switch_RA412C1100; MPN 1802.2504

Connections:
+5V: J3.1, PS1.3 (V+)
/L_F: F1.2, PS1.2 (AC/L), RV1.1
/L_IN: J1.2, S1.1
/L_SW: F1.1, J1.1, S1.1a (2)
/N_IN: J2.1, S1.2 (3)
/N_SW: J2.2, PS1.1 (AC/N), RV1.2, S1.2a (4)
GND: J3.2, PS1.4 (V-)

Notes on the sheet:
EU mains board (docs/DESIGN.md D-36): S1 (Marquardt 1802.2504) breaks line and neutral of the load between the WAGO blocks J1 (L) and J2 (N). F1 / RV1 / PS1 (Zettler ZPI03S0500WC) from the switched side; PS1's outputs on the 5 V island (relief slot), J3 header to the pin board.

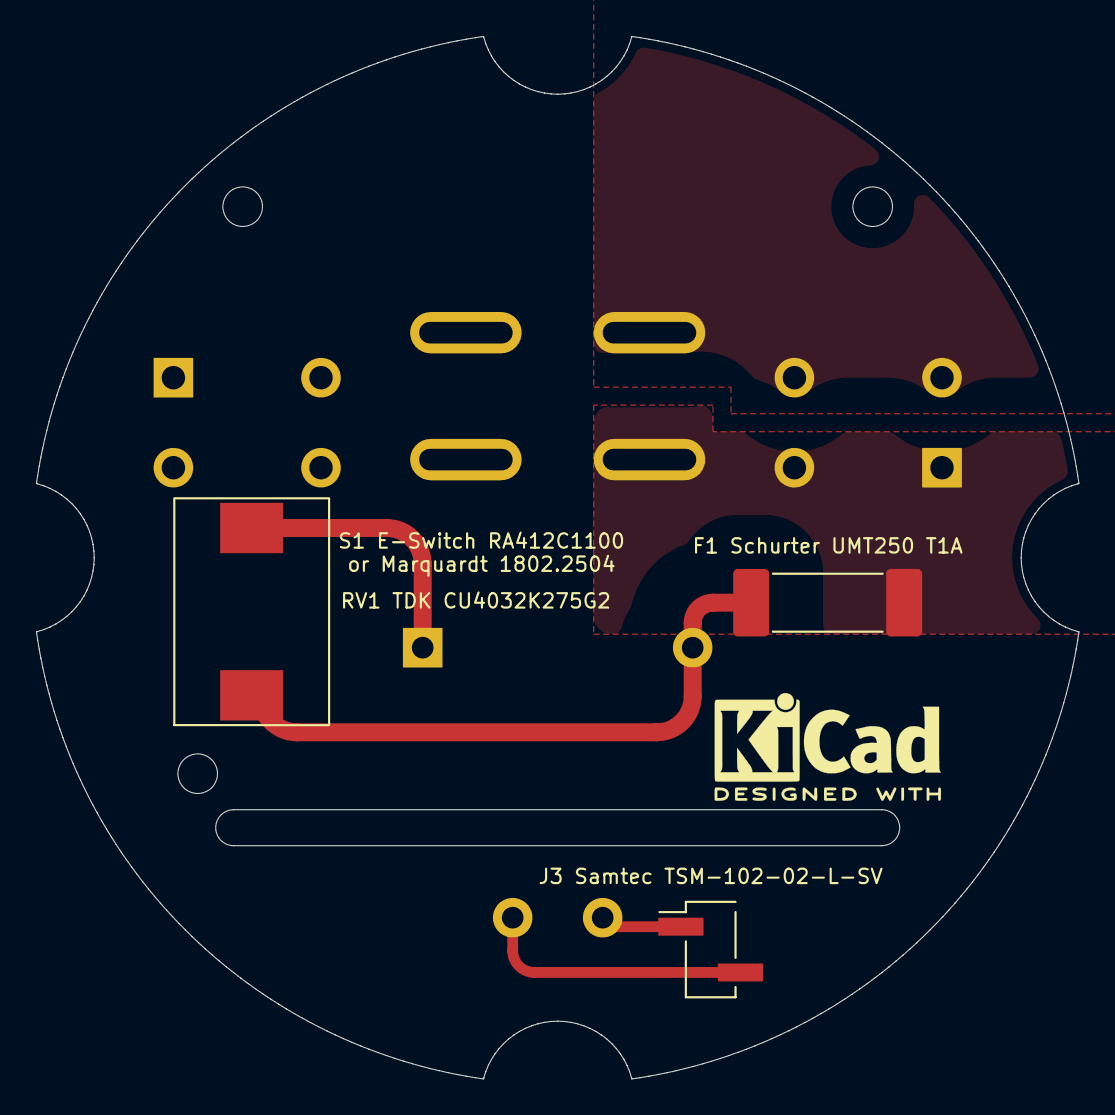
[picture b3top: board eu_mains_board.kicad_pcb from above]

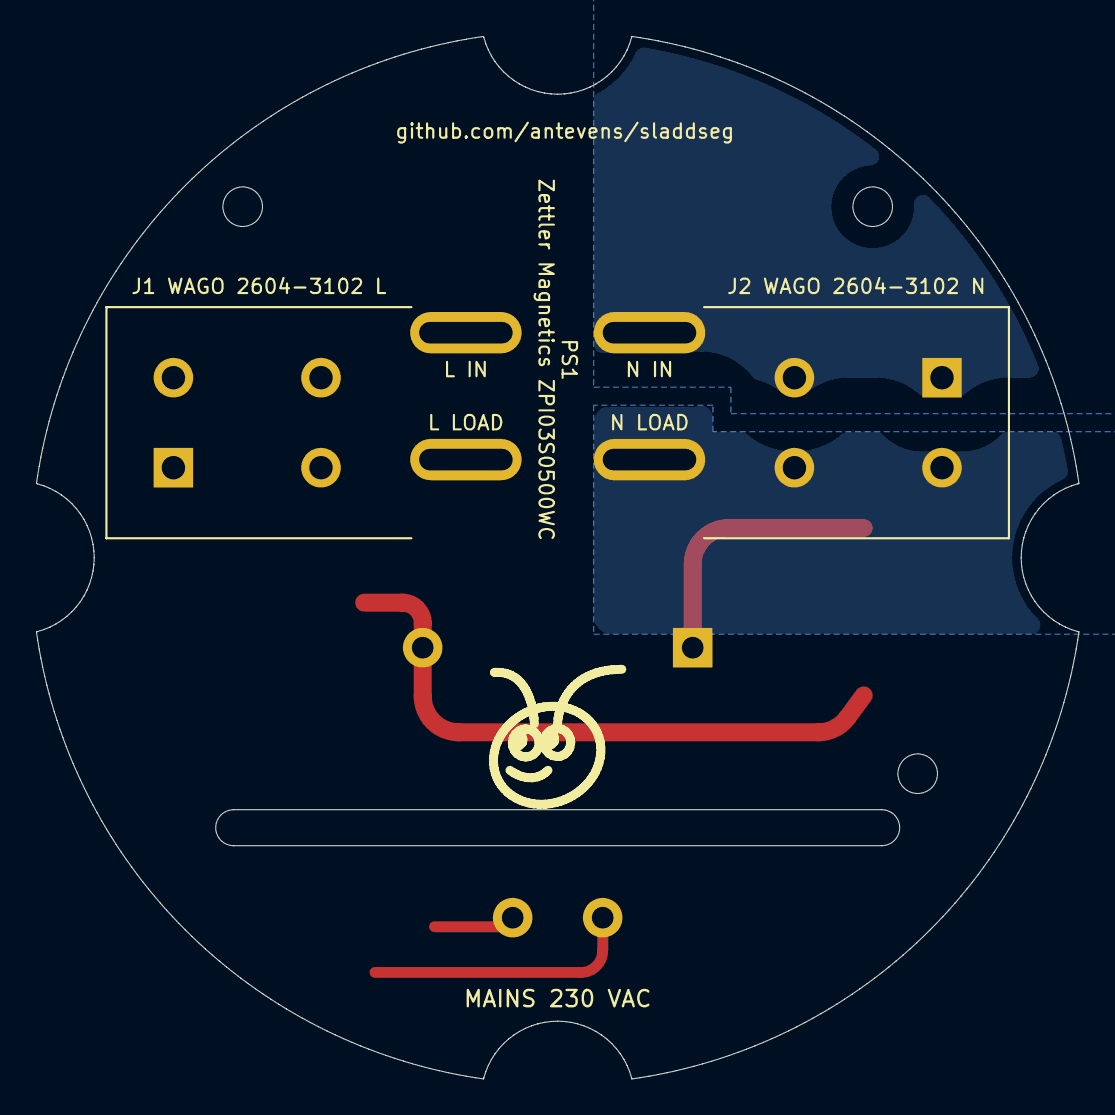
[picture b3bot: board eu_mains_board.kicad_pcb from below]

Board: 2 copper layers, 57.9 x 57.9 mm, 12 parts (4 on the bottom side), 7 nets.

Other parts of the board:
LOGO1: Ant_Logo_8mm_SilkScreen
LOGO2: KiCad-Logo2_5mm_SilkScreen
